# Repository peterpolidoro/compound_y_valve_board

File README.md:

- [Repository Information](#org6a90782)
  - [Description](#orgf515803)
- [Images](#org8e21772)
- [Schematic](#org4408de4)
- [Gerbers](#org2b33e62)
- [Bill of Materials](#org6bcd28f)
  - [PCB Parts](#orgb6b8d32)
  - [Supplemental Parts](#org0a79596)
  - [Vendor Parts Lists](#orgea142e0)
- [Supplemental Documentation](#org34a7f76)
  - [Assembly Instructions](#orgbe6a6db)
- [Manufacturing Archive](#org17d4580)

# Repository Information

-   **Name:** y\_arena\_valve\_controller
-   **Version:** 1.3
-   **License:** Open-Source Hardware
-   **URL:** <https://github.com/janelia-kicad/y_arena_valve_controller>
-   **Author:** Peter Polidoro
-   **Email:** peterpolidoro@gmail.com

## Description

This board controls the y-arena valves for the Turner lab.

## Documentation

<https://janelia-kicad.github.io/y_arena_odor_controller>

# Images

# Schematic

[./schematic/y\_arena\_valve\_controller.pdf](./schematic/y_arena_valve_controller.pdf)

# Gerbers

# Bill of Materials

## PCB Parts

| Item | Reference(s)                        | Quantity | Manufacturer                    | Manufacturer Part Number | Vendor   | Vendor Part Number   | Description                    | Package            |
|---- |----------------------------------- |-------- |------------------------------- |------------------------ |-------- |-------------------- |------------------------------ |------------------ |
| 1    | C1                                  | 1        | TDK Corporation                 | C2012X5R1V106K085AC      | Digi-Key | 445-14417-1-ND       | CAP CER 10UF 35V X5R           | 0805 (2012 Metric) |
| 2    | C10 C12 C14 C16 C18 C2 C4 C6 C8     | 9        | Vishay Sprague                  | 298D105X0016K2T          | Digi-Key | 718-1618-1-ND        | CAP TANT 1UF 20% 16V           | 0402               |
| 3    | C11 C13 C15 C17 C19 C3 C5 C7 C9     | 9        | Murata Electronics              | GCM155R71H153JA55D       | Digi-Key | 490-16428-1-ND       | CAP CER 0.015UF 50V X7R 0402   | 0402               |
| 4    | D1                                  | 1        | Nexperia USA Inc.               | PMEG045V100EPDZ          | Digi-Key | 1727-1904-1-ND       | DIODE SCHOTTKY 45V 10A         | CFP15              |
| 5    | D10 D12 D14 D16 D18 D20 D4 D6 D8    | 9        | Comchip Technology              | CDBQR0230L               | Digi-Key | 641-1275-1-ND        | DIODE SCHOTTKY 30V 200MA       | 0402               |
| 6    | D11 D13 D15 D17 D19 D3 D5 D7 D9 D2  | 10       | Diodes Incorporated             | BAS116LPH4-7B            | Digi-Key | BAS116LPH4-7BDICT-ND | DIODE GEN PURP 85V 215MA 2DFN  | 0402               |
| 7    | L1 L10 L2 L3 L4 L5 L6 L7 L8 L9      | 10       | Lite-On Inc.                    | LTST-C170GKT             | Digi-Key | 160-1179-1-ND        | LED GREEN CLEAR SMD            | 0805 (2012 Metric) |
| 8    | P1                                  | 1        | CUI Devices                     | PJ-036AH-SMT-TR          | Digi-Key | CP-036AHPJCT-ND      | CONN PWR JACK 2X5.5MM SOLDER   |                    |
| 9    | R1 R11 R14 R17 R2 R20 R23 R26 R5 R8 | 10       | Panasonic Electronic Components | ERJ-PA2J391X             | Digi-Key | P124568CT-ND         | RES SMD 390 OHM 5% 1/5W        | 0402               |
| 10   | R10 R13 R16 R19 R22 R25 R28 R4 R7   | 9        | Panasonic Electronic Components | ERJ-2RKF2053X            | Digi-Key | P205KLCT-ND          | RES SMD 205K OHM 1% 1/10W 0402 | 0402               |
| 11   | R12 R15 R18 R21 R24 R27 R3 R6 R9    | 9        | Panasonic Electronic Components | ERJ-2RKF1503X            | Digi-Key | P150KLCT-ND          | RES SMD 150K OHM 1% 1/10W 0402 | 0402               |
| 12   | S1 S2 S3 S4 S5 S6 S7 S8 S9 TEENSY1  | 46       | Mill-Max Manufacturing Corp     | 0305-0-15-15-47-27-10-0  | Digi-Key | ED90331-ND           | CONN PIN RCPT .025-.037 SOLDER |                    |
| 13   | SW1                                 | 1        | E-Switch                        | 500ASSP1SM6QE            | Digi-Key | EG5810CT-ND          | SWITCH SLIDE SPDT 3A 120V      |                    |
| 14   | U1 U2 U3 U4 U5 U6 U7 U8 U9          | 9        | Texas Instruments               | DRV103U                  | Digi-Key | 296-11622-ND         | IC LO-SIDE DRIVER PWM 8SOIC    | 8SOIC              |
|      | FID1 FID2 FID3 FID4 MH1 MH2 MH3     | 7        |                                 |                          |          |                      |                                |                    |

## Supplemental Parts

| Item | Quantity | Manufacturer                 | Manufacturer Part Number        | Vendor   | Vendor Part Number                 | Description                      |
|---- |-------- |---------------------------- |------------------------------- |-------- |---------------------------------- |-------------------------------- |
| 1    | 1        | SparkFun Electronics         | DEV-15583                       | Digi-Key | 1568-DEV-15583-ND                  | TEENSY 4.0                       |
| 2    | 2        | Molex                        | 0022284146                      | Digi-Key | WM24210-ND                         | CONN HEADER VERT 14POS 2.54MM    |
| 3    | 1        | Qualtek                      | 3021075-03                      | Digi-Key | Q1223-ND                           | USB 2.0 A MALE TO USB 2.0 MICRO  |
| 4    | 1        | Tripp Lite                   | U222-004-R                      | Digi-Key | TL430-ND                           | HUB USB 4-PORT 2.0 & 1.1         |
| 5    | 1        | MEAN WELL USA Inc.           | GST60A12-P1J                    | Digi-Key | 1866-2149-ND                       | AC/DC DESKTOP ADAPTER 12V 60W    |
| 6    | 1        | MEAN WELL USA Inc.           | YP12+YC12                       | Digi-Key | 1866-5006-ND                       | CORD IEC 320-C13 6FT BLACK       |
| 7    | 1        | Tensility International Corp | 10-02739                        | Digi-Key | 839-1474-ND                        | SPLITTER 5.5X2.1MM F TO X4 M     |
| 8    | 1        | Tensility International Corp | CA-2219                         | Digi-Key | CP-2219-ND                         | CABLE ASSY 5.5X2.1MM M/F R/A 3FT |
| 9    | 1        | Raspberry Pi                 | RASPBERRY PI 4B/4GB             | Digi-Key | 1690-RASPBERRYPI4B/4GB-ND          | RASPBERRY PI 4B/4GB              |
| 10   | 1        | Raspberry Pi                 | RPI USB-C POWER SUPPLY BLACK US | Digi-Key | 1690-RPIUSB-CPOWERSUPPLYBLACKUS-ND | RPI USB-C POWER SUPPLY BLACK US  |
| 11   | 1        | Raspberry Pi                 | RASPBERRY PI 4 CASE BLACK/GREY  | Digi-Key | 1690-RASPBERRYPI4CASEBLACK/GREY-ND | RASPBERRY PI 4 CASE BLACK/GREY   |
| 12   | 1        | Raspberry Pi                 | 8997466                         | Digi-Key | 1690-1007-ND                       | RASPBERRY PI 7" TOUCH SCREEN LCD |
| 13   | 1        | ATP Electronics Inc          | AF32GUD3-OEM                    | Digi-Key | AF32GUD3-OEM-ND                    | MEM CARD MICROSD 32GB CLS 10 MLC |
| 14   | 1        | Tripp Lite                   | U352-000-MD                     | Digi-Key | TL825-ND                           | USB 3.0 MULTI-DRIVE SD CF MS     |
| 15   | 1        | Tripp Lite                   | U336-000-R                      | Digi-Key | TL824-ND                           | USB 3.0 TO ETHERNET ADAPTER      |
| 16   | 1        | Assmann WSW Components       | A-MCSSP60010/B                  | Digi-Key | AE10190-ND                         | CABLE MOD 8P8C PLUG-PLUG 3.28FT  |

## Vendor Parts Lists

[./bom/Digi-Key\_parts.csv](./bom/Digi-Key_parts.csv)

[./bom/supplemental\_Digi-Key\_parts.csv](./bom/supplemental_Digi-Key_parts.csv)

# Supplemental Documentation

## Assembly Instructions

Solder surface mount and through hole components onto the pcb.

# Manufacturing Archive

Send manufacturing zip file to your favorite PCB manufacturer for fabrication.

[./manufacturing/y\_arena\_valve\_controller\_v1.3.zip](./manufacturing/y_arena_valve_controller_v1.3.zip)

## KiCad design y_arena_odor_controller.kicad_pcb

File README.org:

#+TITLE: y_arena_odor_controller
#+AUTHOR: Peter Polidoro
#+EMAIL: peterpolidoro@gmail.com

** Repository Information

   - Name :: y_arena_odor_controller
   - Version :: 1.3
   - License :: Open-Source Hardware
   - URL :: https://github.com/janelia-kicad/y_arena_odor_controller
   - Author :: Peter Polidoro
   - Email :: peterpolidoro@gmail.com

** Description

   This board controls the y-arena odors for the Janelia Turner lab.

** Documentation

   https://janelia-kicad.github.io/y_arena_odor_controller

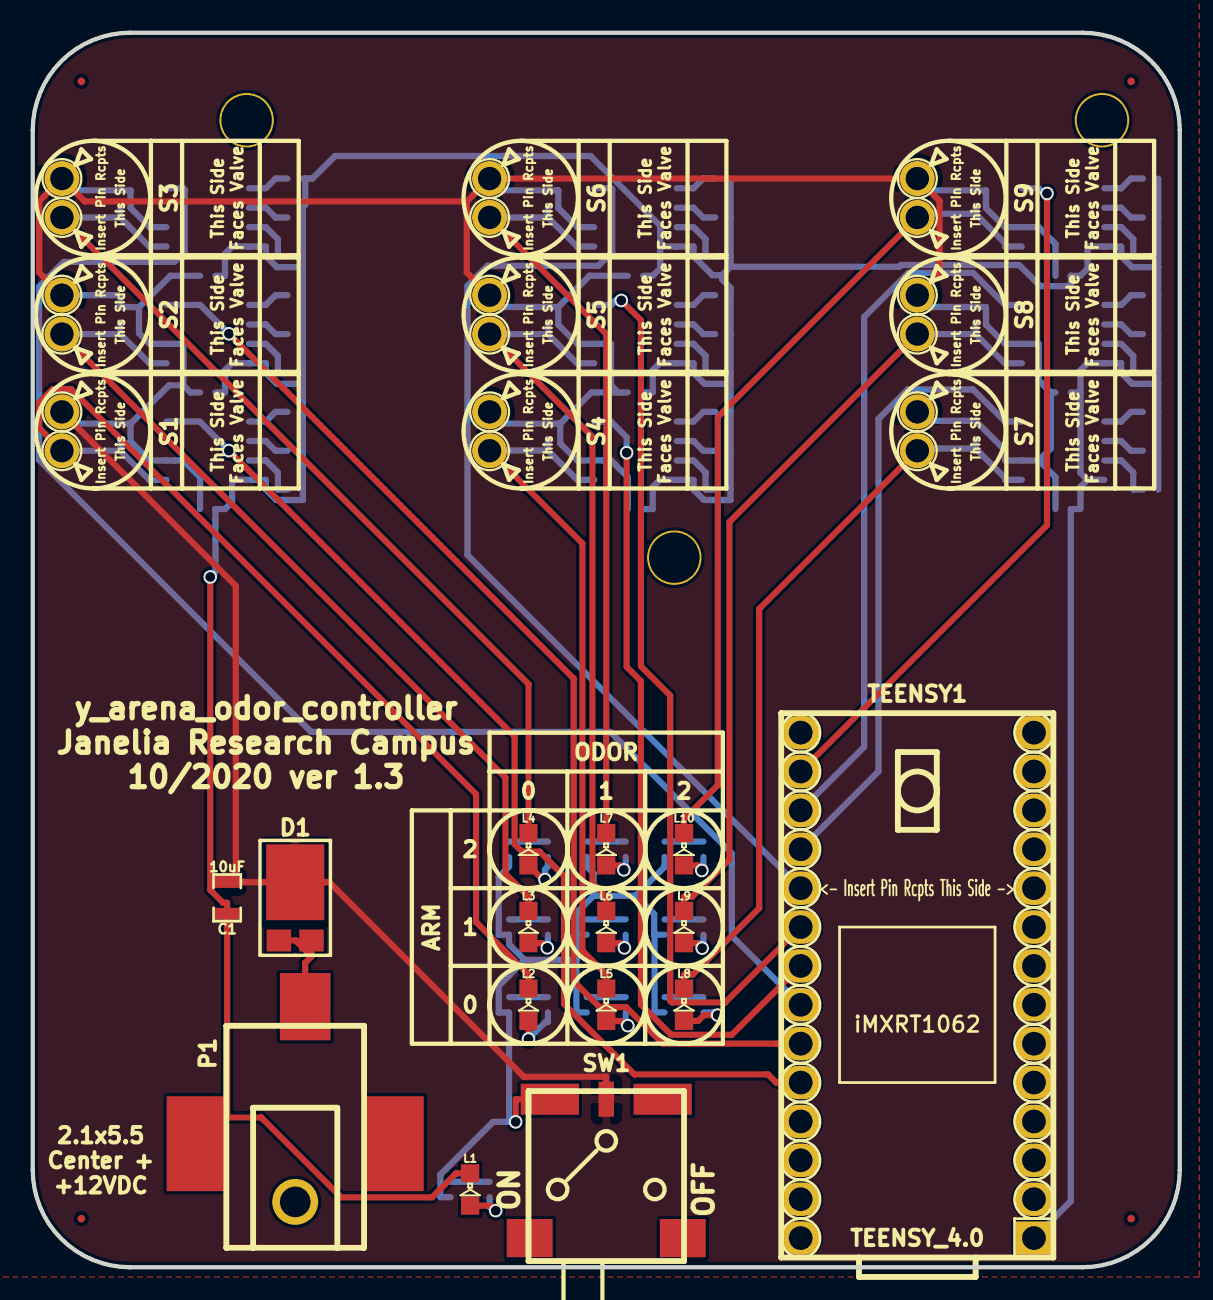
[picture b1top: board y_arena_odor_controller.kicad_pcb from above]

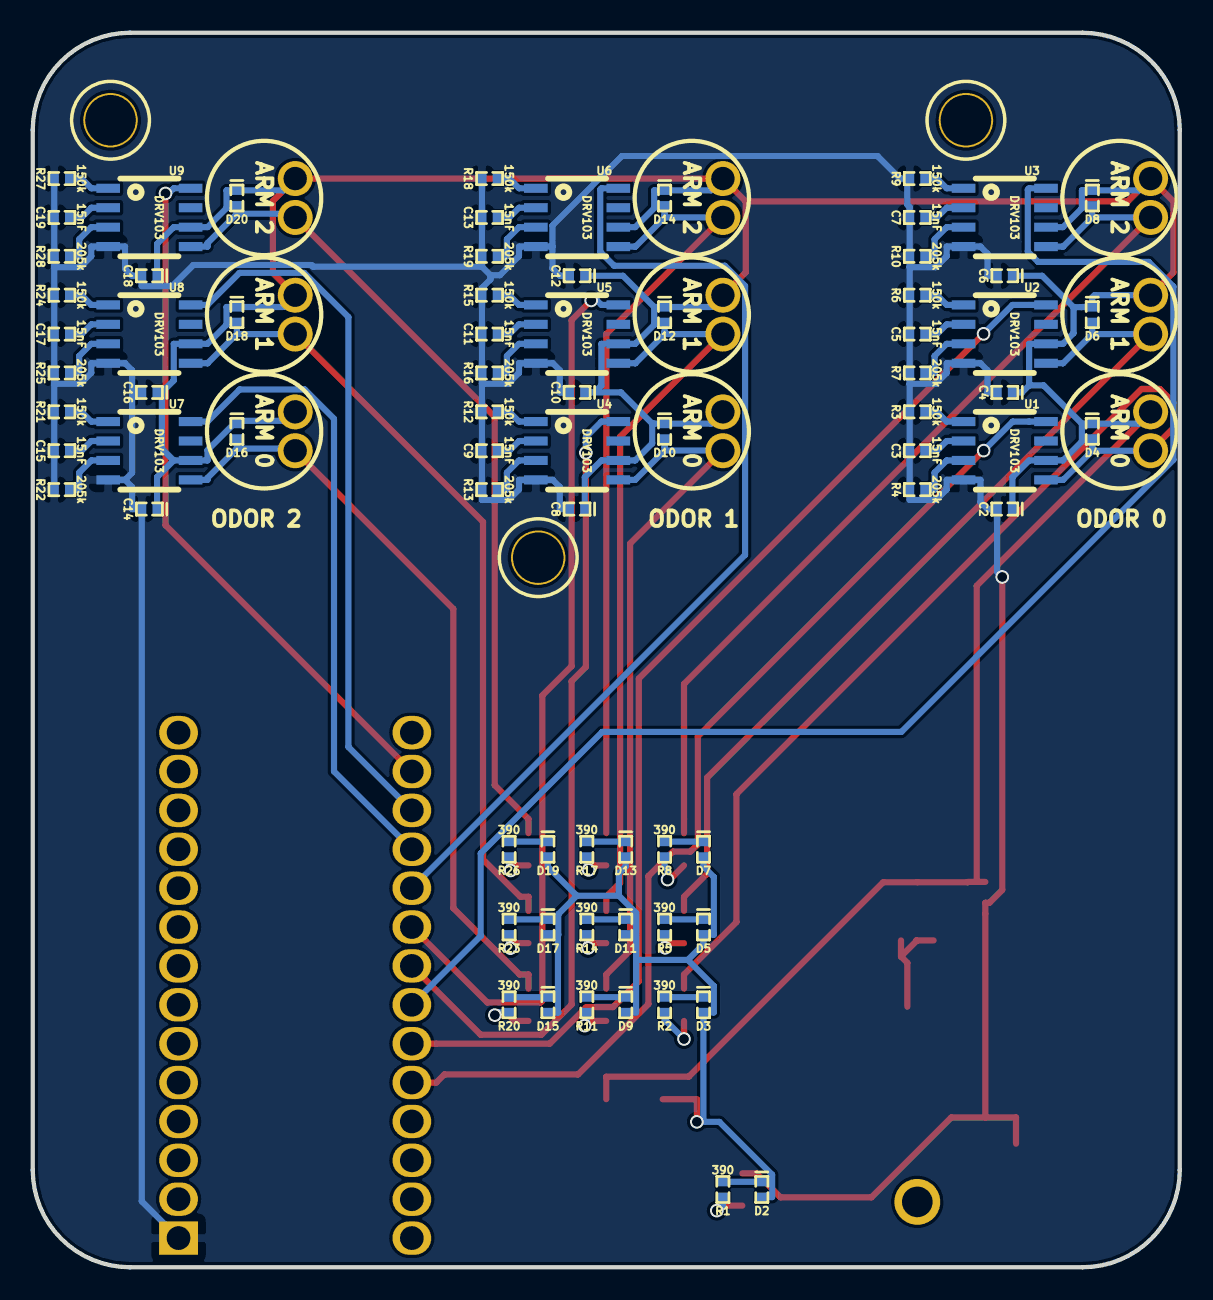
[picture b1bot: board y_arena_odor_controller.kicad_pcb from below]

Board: 2 copper layers, 74.9 x 80.6 mm, 105 parts (77 on the bottom side), 69 nets.

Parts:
C1: 10uF; SM0805
C2, C4, C6, C8, C10, C12, C14, C16, C18: 1uF; SM0402_POL
C3, C5, C7, C9, C11, C13, C15, C17, C19: 15nF; SM0402
D1: DIODE_SCHOTTKY_45V_10A; CFP15
D2, D3, D5, D7, D9, D11, D13, D15, D17, D19: DIODE_LOW_REV_CURRENT_0402; SM0402_POL
D4, D6, D8, D10, D12, D14, D16, D18, D20: DIODE_SCHOTTKY_0402; SM0402_POL
FID1, FID2, FID3, FID4: FIDUCIAL
L1, L2, L3, L4, L5, L6, L7, L8, L9, L10: LED_GRN; LED0805
MH1, MH2, MH3: VAL**; MOUNTING_HOLE_4-40
P1: PWR_JACK_2.1x5.5_SMD_RA; DCJACK_3PAD_SMD_RA
R1, R2, R5, R8, R11, R14, R17, R20, R23, R26: 390; SM0402
R3, R6, R9, R12, R15, R18, R21, R24, R27: 150k; SM0402
R4, R7, R10, R13, R16, R19, R22, R25, R28: 205k; SM0402
S1, S2, S3, S4, S5, S6, S7, S8, S9: VAL**; LEECO_LHDB
SW1: SPDT_SLIDE_500A_SM
TEENSY1: TEENSY_4.0
U1, U2, U3, U4, U5, U6, U7, U8, U9: DRV103; SOIC_8

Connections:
/ARM_0_ODOR_0: TEENSY1.22, U1.8
/ARM_0_ODOR_1: TEENSY1.21, U2.8
/ARM_0_ODOR_2: TEENSY1.20, U3.8
/ARM_1_ODOR_0: TEENSY1.19, U4.8
/ARM_1_ODOR_1: TEENSY1.18, U5.8
/ARM_1_ODOR_2: TEENSY1.17, U6.8
/ARM_2_ODOR_0: TEENSY1.16, U7.8
/ARM_2_ODOR_1: TEENSY1.15, U8.8
/ARM_2_ODOR_2: TEENSY1.14, U9.8
/Vled: D2.2, D3.2, D5.2, D7.2, D9.2, D11.2, D13.2, D15.2, D17.2, D19.2, SW1.1
/odor_0/SH: D4.2, L2.2, S1.1, U1.5
/odor_1/SH: D6.2, L3.2, S2.1, U2.5
/odor_2/SH: D8.2, L4.2, S3.1, U3.5
/odor_3/SH: D10.2, L5.2, S4.1, U4.5
/odor_4/SH: D12.2, L6.2, S5.1, U5.5
/odor_5/SH: D14.2, L7.2, S6.1, U6.5
/odor_6/SH: D16.2, L8.2, S7.1, U7.5
/odor_7/SH: D18.2, L9.2, S8.1, U8.5
/odor_8/SH: D20.2, L10.2, S9.1, U9.5
GND: C1.2, C2.2, C3.2, C4.2, C5.2, C6.2, C7.2, C8.2, C9.2, C10.2, C11.2, C12.2, C13.2, C14.2, C15.2, C16.2, C17.2, C18.2, C19.2, L1.2, P1.2, R3.2, R4.2, R6.2, R7.2, R9.2, R10.2, R12.2, R13.2, R15.2, R16.2, R18.2, R19.2, R21.2, R22.2, R24.2, R25.2, R27.2, R28.2, TEENSY1.GND, U1.4, U2.4, U3.4, U4.4, U5.4, U6.4, U7.4, U8.4, U9.4
unnamed: C3.1, U1.2
unnamed: C5.1, U2.2
unnamed: C7.1, U3.2
unnamed: C9.1, U4.2
unnamed: C11.1, U5.2
unnamed: C13.1, U6.2
unnamed: C15.1, U7.2
unnamed: C17.1, U8.2
unnamed: C19.1, U9.2
unnamed: D2.1, R1.1
unnamed: D3.1, R2.1
unnamed: D5.1, R5.1
unnamed: D7.1, R8.1
unnamed: D9.1, R11.1
unnamed: D11.1, R14.1
unnamed: D13.1, R17.1
unnamed: D15.1, R20.1
unnamed: D17.1, R23.1
unnamed: D19.1, R26.1
unnamed: L1.1, R1.2
unnamed: L2.1, R2.2
unnamed: L3.1, R5.2
unnamed: L4.1, R8.2
unnamed: L5.1, R11.2
unnamed: L6.1, R14.2
unnamed: L7.1, R17.2
unnamed: L8.1, R20.2
unnamed: L9.1, R23.2
unnamed: L10.1, R26.2
unnamed: R3.1, U1.1
unnamed: R4.1, U1.3
unnamed: R6.1, U2.1
unnamed: R7.1, U2.3
unnamed: R9.1, U3.1
unnamed: R10.1, U3.3
unnamed: R12.1, U4.1
unnamed: R13.1, U4.3
unnamed: R15.1, U5.1
unnamed: R16.1, U5.3
unnamed: R18.1, U6.1
unnamed: R19.1, U6.3
unnamed: R21.1, U7.1
unnamed: R22.1, U7.3
unnamed: R24.1, U8.1
unnamed: R25.1, U8.3
unnamed: R27.1, U9.1
unnamed: R28.1, U9.3
VAA: D1.2, P1.1
VCC: C1.1, C2.1, C4.1, C6.1, C8.1, C10.1, C12.1, C14.1, C16.1, C18.1, D1.1, D4.1, D6.1, D8.1, D10.1, D12.1, D14.1, D16.1, D18.1, D20.1, S1.2, S2.2, S3.2, S4.2, S5.2, S6.2, S7.2, S8.2, S9.2, SW1.2, U1.6, U2.6, U3.6, U4.6, U5.6, U6.6, U7.6, U8.6, U9.6

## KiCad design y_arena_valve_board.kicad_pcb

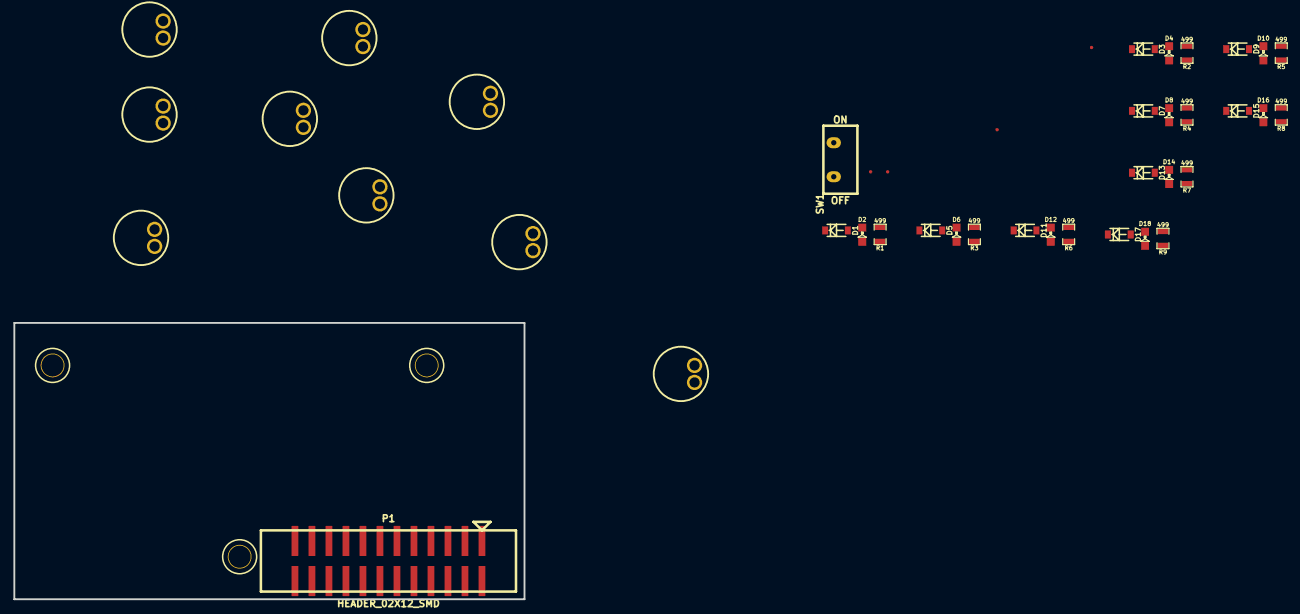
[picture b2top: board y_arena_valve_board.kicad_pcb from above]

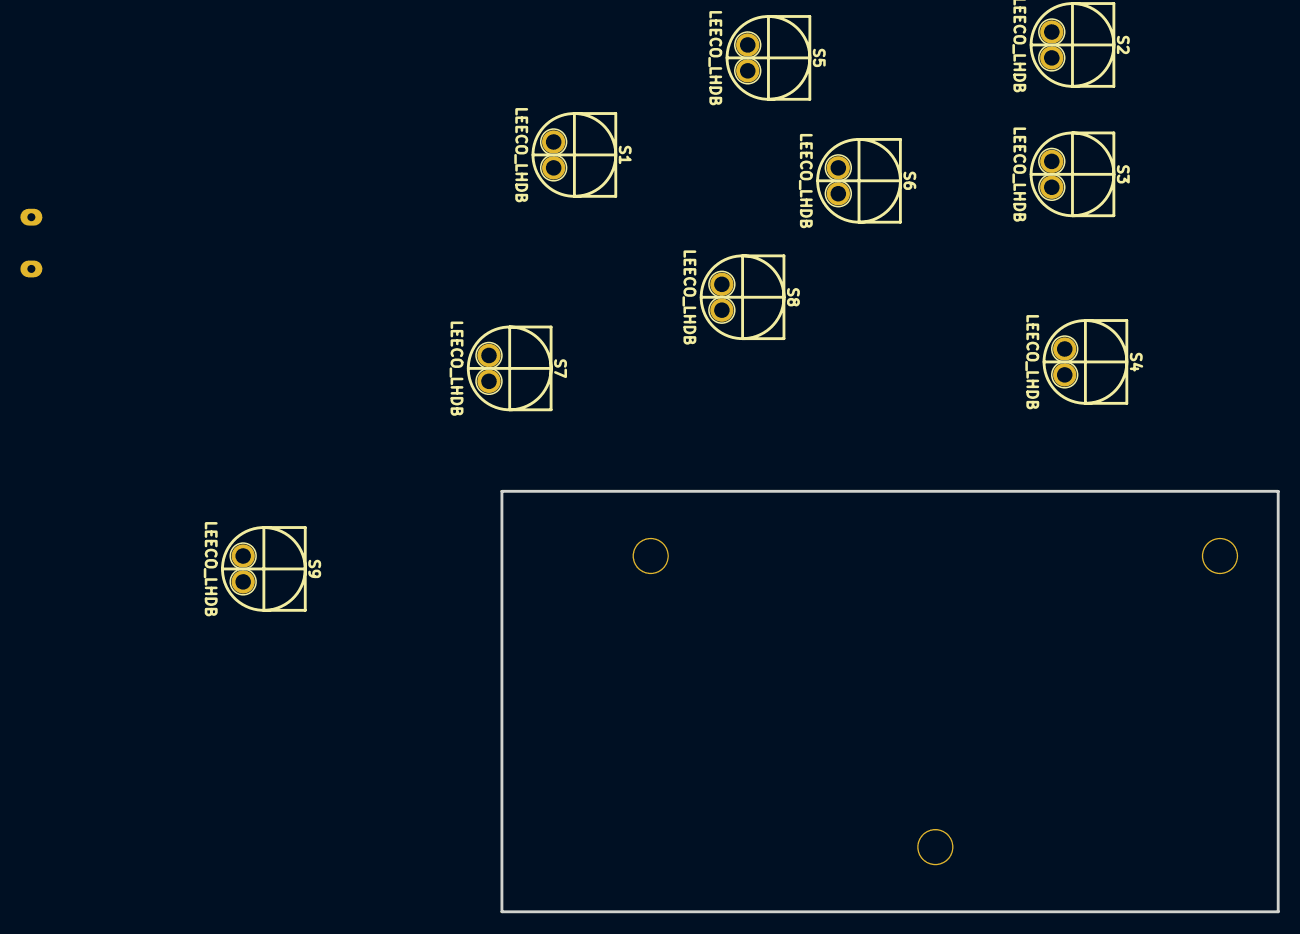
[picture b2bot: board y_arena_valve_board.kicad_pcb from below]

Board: 2 copper layers, 76.2 x 41.3 mm, 45 parts (9 on the bottom side), 29 nets, no tracks yet.

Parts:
D1, D3, D5, D7, D9, D11, D13, D15, D17: diode_low_rev_current; SOD-123
D2, D4, D6, D8, D10, D12, D14, D16, D18: LED_GRN; LED0805
FID1, FID2, FID3, FID4: FIDUCIAL
MH1, MH2, MH3: MOUNTING_HOLE_4-40
P1: HEADER_02X12_SMD; HEADER_02x12_SMD
R1, R2, R3, R4, R5, R6, R7, R8, R9: 499; SM0805
S1, S2, S3, S4, S5, S6, S7, S8, S9: LEECO_LHDB
SW1: SPST_SLIDE_AS

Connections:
/VALVE_0: D2.2, P1.2, S1.2
/VALVE_1: D4.2, P1.4, S2.2
/VALVE_2: D6.2, P1.6, S3.2
/VALVE_3: D8.2, P1.8, S4.2
/VALVE_4: D10.2, P1.10, S5.2
/VALVE_5: D12.2, P1.12, S6.2
/VALVE_6: D14.2, P1.14, S7.2
/VALVE_7: D16.2, P1.16, S8.2
/VALVE_8: D18.2, P1.18, S9.2
LED_PWR: D1.2, D3.2, D5.2, D7.2, D9.2, D11.2, D13.2, D15.2, D17.2, SW1.3
unnamed: D1.1, R1.1
unnamed: D2.1, R1.2
unnamed: D3.1, R2.1
unnamed: D4.1, R2.2
unnamed: D5.1, R3.1
unnamed: D6.1, R3.2
unnamed: D7.1, R4.1
unnamed: D8.1, R4.2
unnamed: D9.1, R5.1
unnamed: D10.1, R5.2
unnamed: D11.1, R6.1
unnamed: D12.1, R6.2
unnamed: D13.1, R7.1
unnamed: D14.1, R7.2
unnamed: D15.1, R8.1
unnamed: D16.1, R8.2
unnamed: D17.1, R9.1
unnamed: D18.1, R9.2
VAA: P1.1, P1.3, P1.5, P1.7, P1.9, P1.11, P1.13, P1.15, P1.17, P1.19, P1.21, P1.23, S1.1, S2.1, S3.1, S4.1, S5.1, S6.1, S7.1, S8.1, S9.1, SW1.1

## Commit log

2020-06-25 Add mechanical files
2020-06-25 Update mechanical files
2020-06-29 Move files
2020-06-29 Moved files
2020-06-29 Progress towards v1.0
2020-06-30 compound_y_valve_board -> y_arena_controller_pi
2020-06-30 Copy components and footprints from power_switch_controller
2020-07-01 Update raspberry_pi_with_power
2020-07-01 y_arena_controller_pi -> y_arena_valve_board
2020-07-01 Add header
2020-07-02 Initial pcb import
2020-07-03 Add footprints to test
2020-07-13 y_arena_valve_board -> y_arena_valve_controller
2020-07-13 Add Teensy 4.0
2020-07-13 Add schematics
2020-07-13 First draft of schematic
2020-07-17 Remove teensy and add power input
2020-07-17 Add phidget
2020-07-18 Rough pcb layout
2020-07-20 Updated libraries
2020-07-20 Update library paths
2020-07-20 Finished schematic v1.0
2020-07-21 Finished ver 1.0
2020-07-21 Progress towards v1.1
2020-07-21 Finished v1.1
2020-07-21 Finishing up BOM
2020-07-22 Add parts to BOM
2020-07-31 Finished schematic v1.2
2020-07-31 Updated parts
2020-08-01 Use 0402 parts instead of 0805
2020-08-01 Ready to route
2020-08-01 Route tracks and zones
2020-08-02 Use surface mount slide switch and barrel jack
2020-08-02 Finished routing
2020-08-02 Documentation ready but flaw in bom
2020-08-03 Finished version 1.2
2020-08-03 Fix name error
2020-08-06 Updated supplemental bom
2020-08-14 Add position file in csv format
2020-08-18 Use new usb hub part
2020-08-19 Rename VALVE lines from VALVE_0 -> ARM_0_VALVE_0
2020-08-19 Update documentation
2020-08-19 Update schematic
2020-09-02 Added board images to documentation
2020-10-21 valve -> odor
2020-10-21 Switch arms from columns to rows and use odor instead of valve
2020-10-21 Fix documentation
2020-11-18 Add board images
2020-11-19 Rotate board images
2020-11-19 Removed submodule generate_kicad_documentation
2020-11-19 Setup mkdocs
2020-11-19 Add ci
2020-11-19 Complete v1.3
2020-11-19 Remove submodule
2020-11-19 Move documentation from README to mkdocs
2020-11-19 Fix typo in README
2020-11-19 Fix yaml spacing
2020-11-19 Fixed broken link
2020-11-20 Fix repo url
2020-11-20 Deployed 5e26965 with MkDocs version: 1.1.2
